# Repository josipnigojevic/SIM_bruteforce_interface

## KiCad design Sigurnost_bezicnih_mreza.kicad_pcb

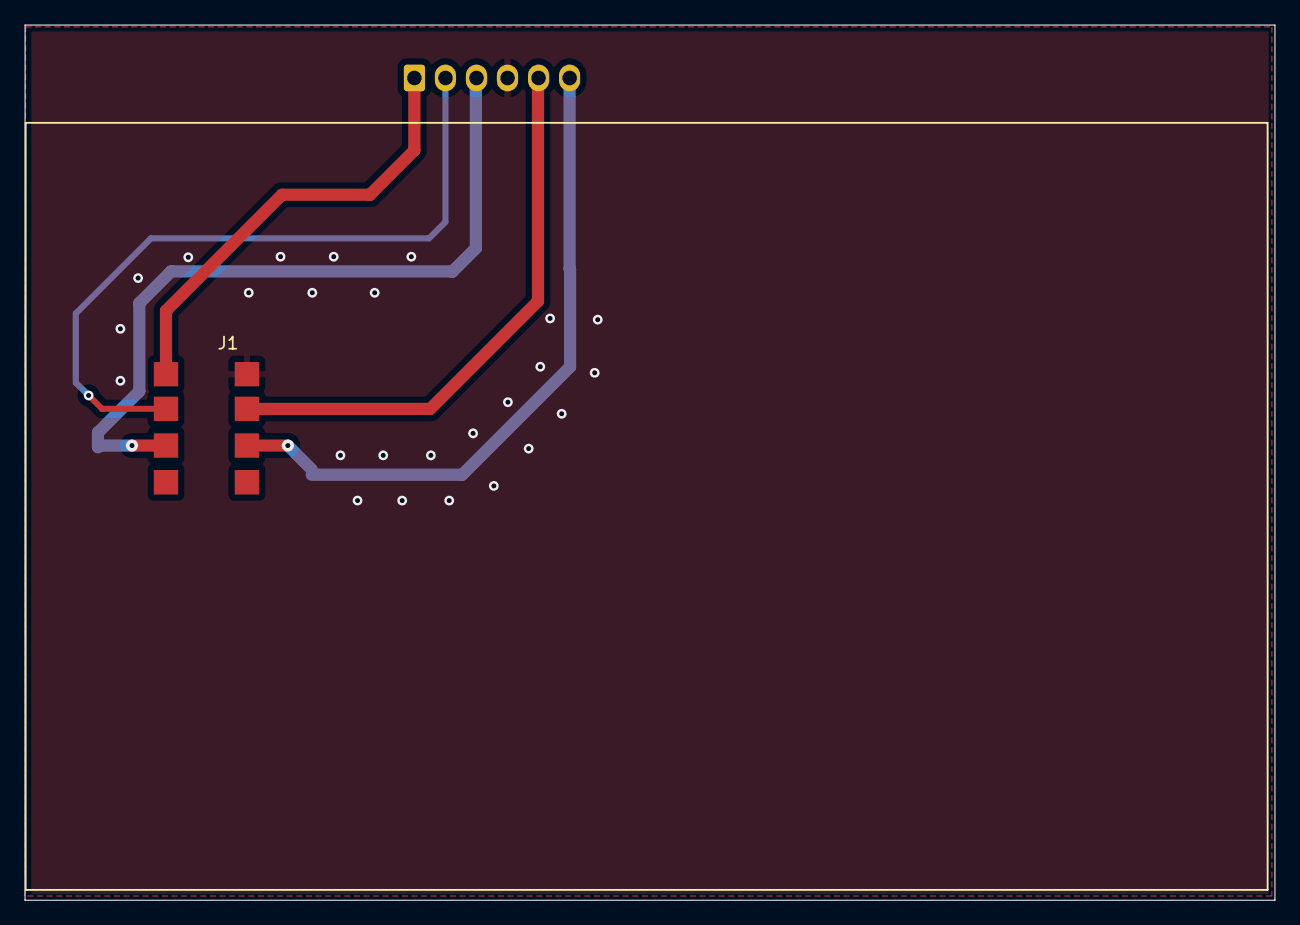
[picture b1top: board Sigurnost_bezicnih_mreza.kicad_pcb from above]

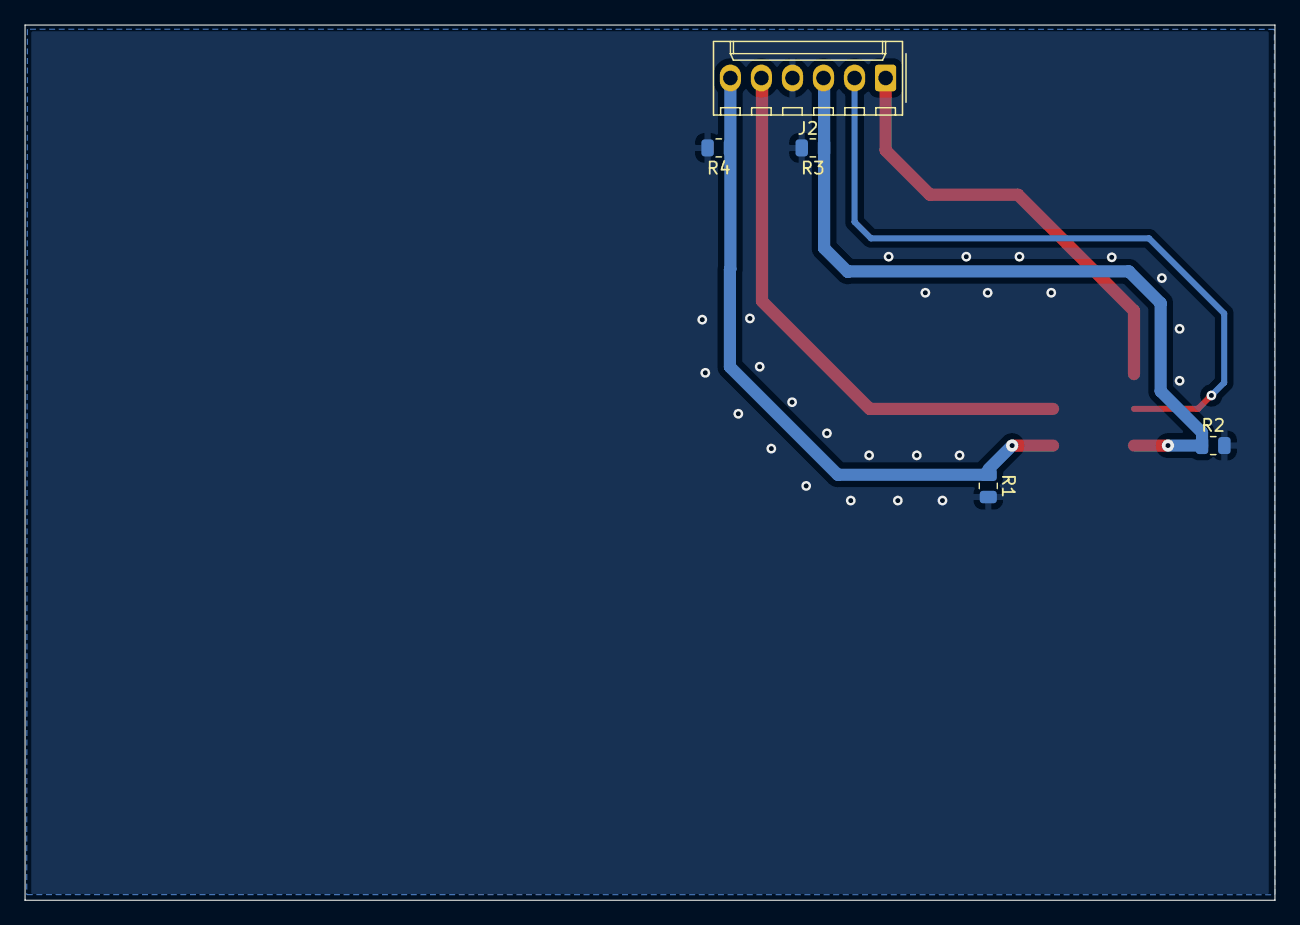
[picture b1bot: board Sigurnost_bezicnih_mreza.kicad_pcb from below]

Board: 2 copper layers, 102.2 x 71.6 mm, 6 parts (5 on the bottom side), 6 nets.

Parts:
J1: SIM_Card; SIM_2
J2: Conn_01x06_Male; Molex_KK-254_AE-6410-06A_1x06_P2.54mm_Vertical
R1, R2, R3, R4: R; R_0805_2012Metric

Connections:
/CLK: J1.3 (CLK), J2.3, R2.1, R3.1
/I/O: J1.5 (GND), J2.6, R1.1, R4.1
/RST: J1.2 (RST), J2.2
/Vcc: J1.1 (VCC), J2.1
/Vpp: J1.6 (VPP), J2.5
GND: J1.8, J2.4, R1.2, R2.2, R3.2, R4.2

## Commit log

2022-12-06 Initial commit, TODO:adjust dimensions
2022-12-06 dimensions adjusted
